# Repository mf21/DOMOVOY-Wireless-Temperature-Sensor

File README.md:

# DOMOVOY Wireless Temperature Sensor
This device is a part of DOMOVOY home automation project

https://www.mf21.ru

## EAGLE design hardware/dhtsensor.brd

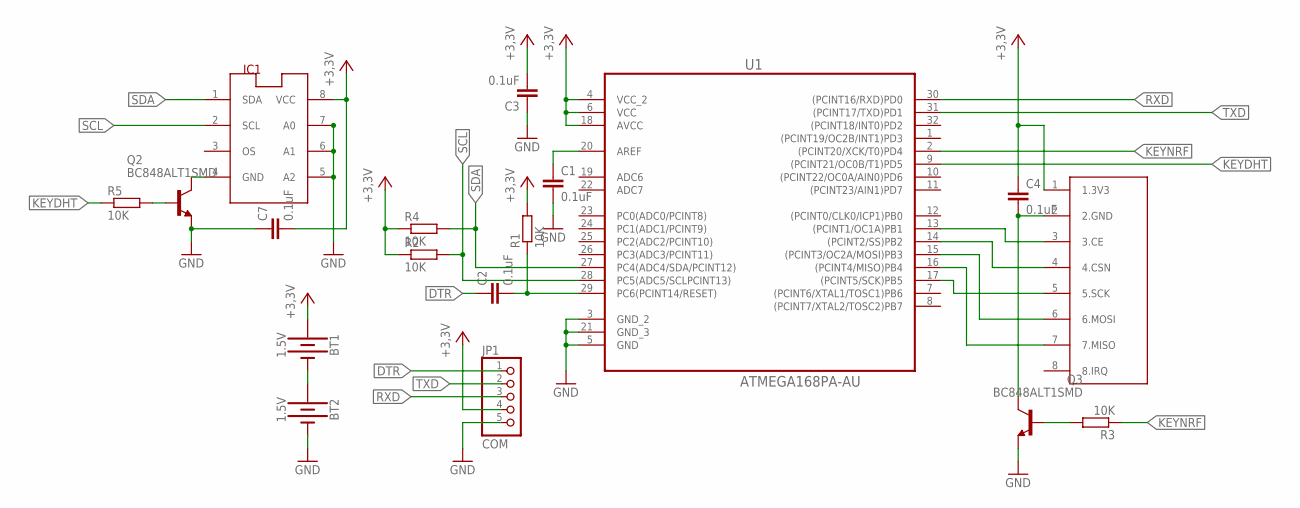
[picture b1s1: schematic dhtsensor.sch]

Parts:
BT1, BT2: 1.5V; BATTERY-AAA-KIT
C1, C2, C3, C4, C7: 0.1uF; C1206
IC1: LM75_ICN; SO8_LM75
JP1: COM; 1X05
Q2, Q3: BC848ALT1SMD; SOT23
R1, R2, R3, R4, R5: 10K; R1206
U1: ATMEGA168PA-AU; QFP80P900X900X120-32N
U$9: NRF24L01+

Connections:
+3,3V: BT1.PWR@1 (+), C3.2, C4.1, C7.2, IC1.8 (VCC), JP1.4, R1.2, R2.1, R4.1, U1.4 (VCC_2), U1.6 (VCC), U1.18 (AVCC), U$9.1 (1.3V3)
DTR: C2.1, JP1.1
GND: BT2.GND@1 (-), C1.2, C3.1, C7.1, IC1.5 (A2), IC1.6 (A1), IC1.7 (A0), JP1.5, Q2.2 (E), Q3.2 (E), U1.3 (GND_2), U1.5 (GND), U1.21 (GND_3)
KEYDHT: R5.1, U1.9 ((PCINT21/OC0B/T1)PD5)
KEYNRF: R3.1, U1.2 ((PCINT20/XCK/T0)PD4)
unnamed: C2.2, R1.1, U1.29 (PC6(PCINT14/RESET))
unnamed: C1.1, U1.20 (AREF)
unnamed: U1.15 ((PCINT3/OC2A/MOSI)PB3), U$9.6 (6.MOSI)
unnamed: U1.16 ((PCINT4/MISO)PB4), U$9.7 (7.MISO)
unnamed: C4.2, Q3.3 (C), U$9.2 (2.GND)
unnamed: BT1.GND@1 (-), BT2.PWR@1 (+)
unnamed: U1.17 ((PCINT5/SCK)PB5), U$9.5 (5.SCK)
unnamed: U1.14 ((PCINT2/SS)PB2), U$9.4 (4.CSN)
unnamed: U1.13 ((PCINT1/OC1A)PB1), U$9.3 (3.CE)
unnamed: Q3.1 (B), R3.2
unnamed: IC1.4 (GND), Q2.3 (C)
unnamed: Q2.1 (B), R5.2
RXD: JP1.3, U1.30 ((PCINT16/RXD)PD0)
SCL: IC1.2 (SCL), R2.2, U1.28 (PC5(ADC5/SCLPCINT13))
SDA: IC1.1 (SDA), R4.2, U1.27 (PC4(ADC4/SDA/PCINT12))
TXD: JP1.2, U1.31 ((PCINT17/TXD)PD1)

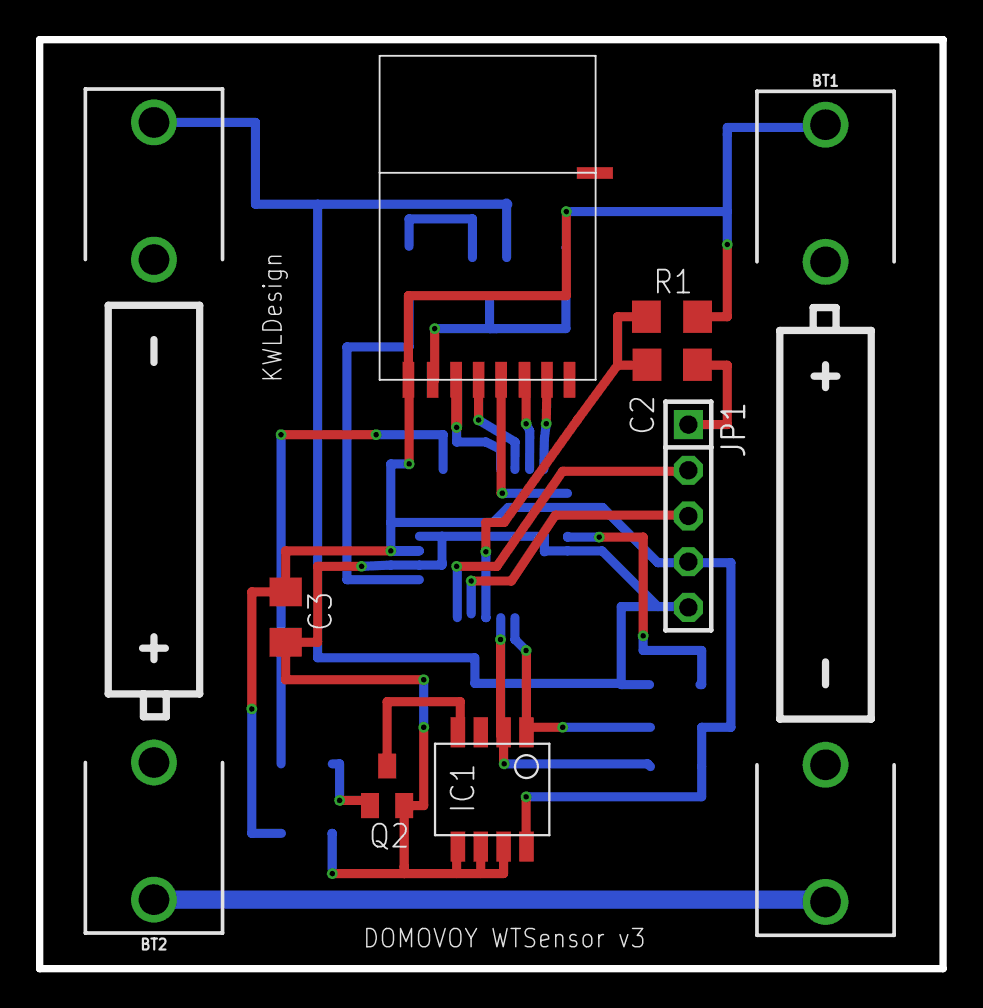
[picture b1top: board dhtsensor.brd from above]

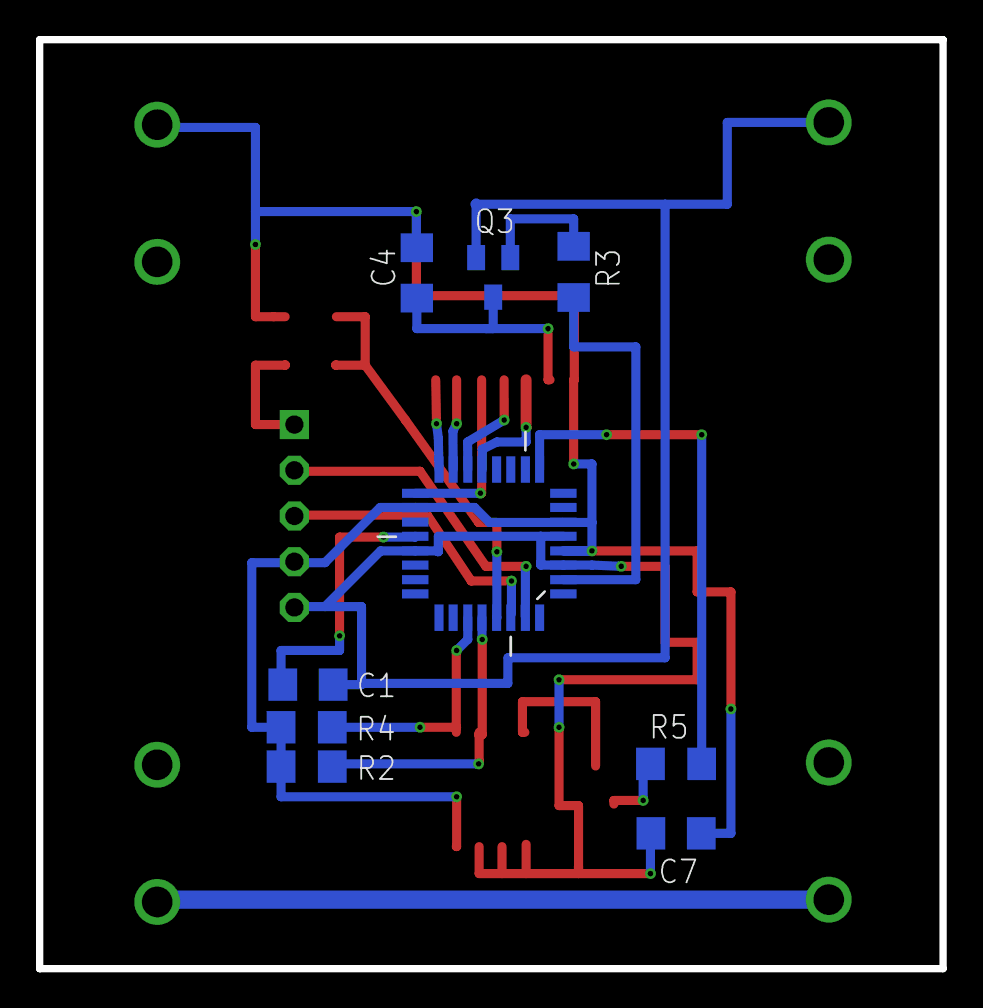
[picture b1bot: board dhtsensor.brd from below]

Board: 2 copper layers, 50.2 x 51.7 mm, 18 parts (9 on the bottom side), 21 nets.

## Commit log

2018-02-10 The first initial commit
2018-02-15 Fix errors
2018-02-23 Fix wireless module settings
2018-02-25 Change readme
2018-06-08 Doc in pdf added
2018-06-08 hardware.pdf changed
2018-06-08 Comment changed

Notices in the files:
parts and their libraries:
SparkFun-Batteries: Licensing: Creative Commons ShareAlike 4.0 International - https://creativecommons.org/licenses/by-sa/4.0
